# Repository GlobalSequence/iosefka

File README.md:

# Iosefka

## Specification

Iosefka is a hybrid digital analog monophonic synthesizer consisting of the following parts:

**Digital audio:**

- 2x wavetable oscillators, capable of interpolated morphing waveforms in the X and Y dimension along 256 hand-picked waveforms in a 16x16 layout
- White noise generator
- Sample-rate reduction and Bit-rate reduction effects
- Loopback digital delay fed from VCA output with feedback and adjustable rate from >3 ms to ~683 ms

**Analog audio:**

- V2140 based analog pole-mixing resonant voltage controlled filter with audio rate frequency modulation selectable between:
    - 2 pole low pass
    - 4 pole low pass
    - 2 pole high pass
    - 2 pole band pass
- LM13700 based voltage controlled amplifier
- External audio input direct into analog section and digital delay

**Step sequencer:**

- 32 step, 24 PPQ performance step sequencer
- Parameterized sequence generator including step chance, length, octave range, and musical scale
- Controls for swing, direction, clock division, first and last step, probability
- Per step Parameter locks for:
    - Note value
    - Step length
    - Velocity value
    - Step Probability
    - Single audio Parameter
- Per step mutes

**Modulation matrix to all audio Parameters:**

- 3x ADSR envelope generators (converted to control voltage for analog modules)
- 3x Low frequency oscillators (converted to control voltage for analog modules)
- Velocity control
- Aftertouch control
- Mod Wheel control
- Breath Control
- Pitch Bend Control

**MIDI Implementation:**

- **MIDI RX**
    - Note and velocity values
    - Realtime messages: clock tick, start, stop
    - CC messages for all audio Parameters (see implementation chart)
    - Modulation control of velocity, aftertouch, mod-wheel
    - Pitch bend with configurable bend range from 1 to 12 semitones
    - Program change (coming soon)
- **MIDI TX**
    - Note and velocity values (from keyboard and sequencer)
    - Realtime messages: clock tick, start, stop

**Patch storage:**

- Store 64 patches of all audio and sequencer Parameters
- Store global MIDI and machine settings

**Oscilloscope:**

- Oscillator phase locked oscilloscope with four 'time' divisions (sample divisions) between 512 to 128 samples.

# Link to the Manual
[Iosefka Manual](https://globalsequence.github.io/iosefka/#)

# Link to the Build Guide
[Build Guide - Iosefka Manual](https://globalsequence.github.io/iosefka/#build_guide/) (It's part of the manual)

# Gerber Files for Ordering the PCBs
This project includes hardware design files, as well as the gerber files which are required for PCB fabrication. The gerber files for the different boards will be found in the locations linked below. There is also a compressed zip file of all of the gerber files within this folder if that's the format your PCB fab of choice requires. 

- [iosefka bottomboard gerbers](./hardware/iosefka_bottomboard/gerbers/)
- [iosefka controlboard gerbers](./hardware/iosefka_controlboard/gerbers/)
- [iosefka motherboard gerbers](./hardware/iosefka_motherboard/gerbers)

# Bill of Materials
The three bills of materials can be found in the hardware folder of this project. 

- [iosefka boms](./hardware/boms/)

# Precompiled firmware
You can download the most current Iosefka firmware from the Releases section of this github repository. Or you can click this link: https://github.com/GlobalSequence/iosefka/releases. 

# A Note to Developers, Engineers, and People Generally Experienced in Programming and Electronics

Take this as a content warning for what you are about to see should you so much as peek into the code of this repository. It may help to frame this whole thing as a hobbyist's project that got way out of hand. I chalk any and all glaring errors up to the fundamental tension of this machine which was 'I want to create/finish this thing' vs. 'I want to learn this stuff'.

It is resoundingly true that the whole is better than the sum of its parts.

With all of that laid bare, please feel free to reach out to me about any suggestions, recommended fixes, or outright errors in both the code and the schematic. I consider the post-release critique the most enduring part of the learning process. globeseq@gmail.com 

# DISCLAIMER
This project is provided for informational and educational purposes only. By using the provided instructions, code, and hardware designs, you acknowledge that you are solely responsible for your own safety and the cost of any materials or components used.

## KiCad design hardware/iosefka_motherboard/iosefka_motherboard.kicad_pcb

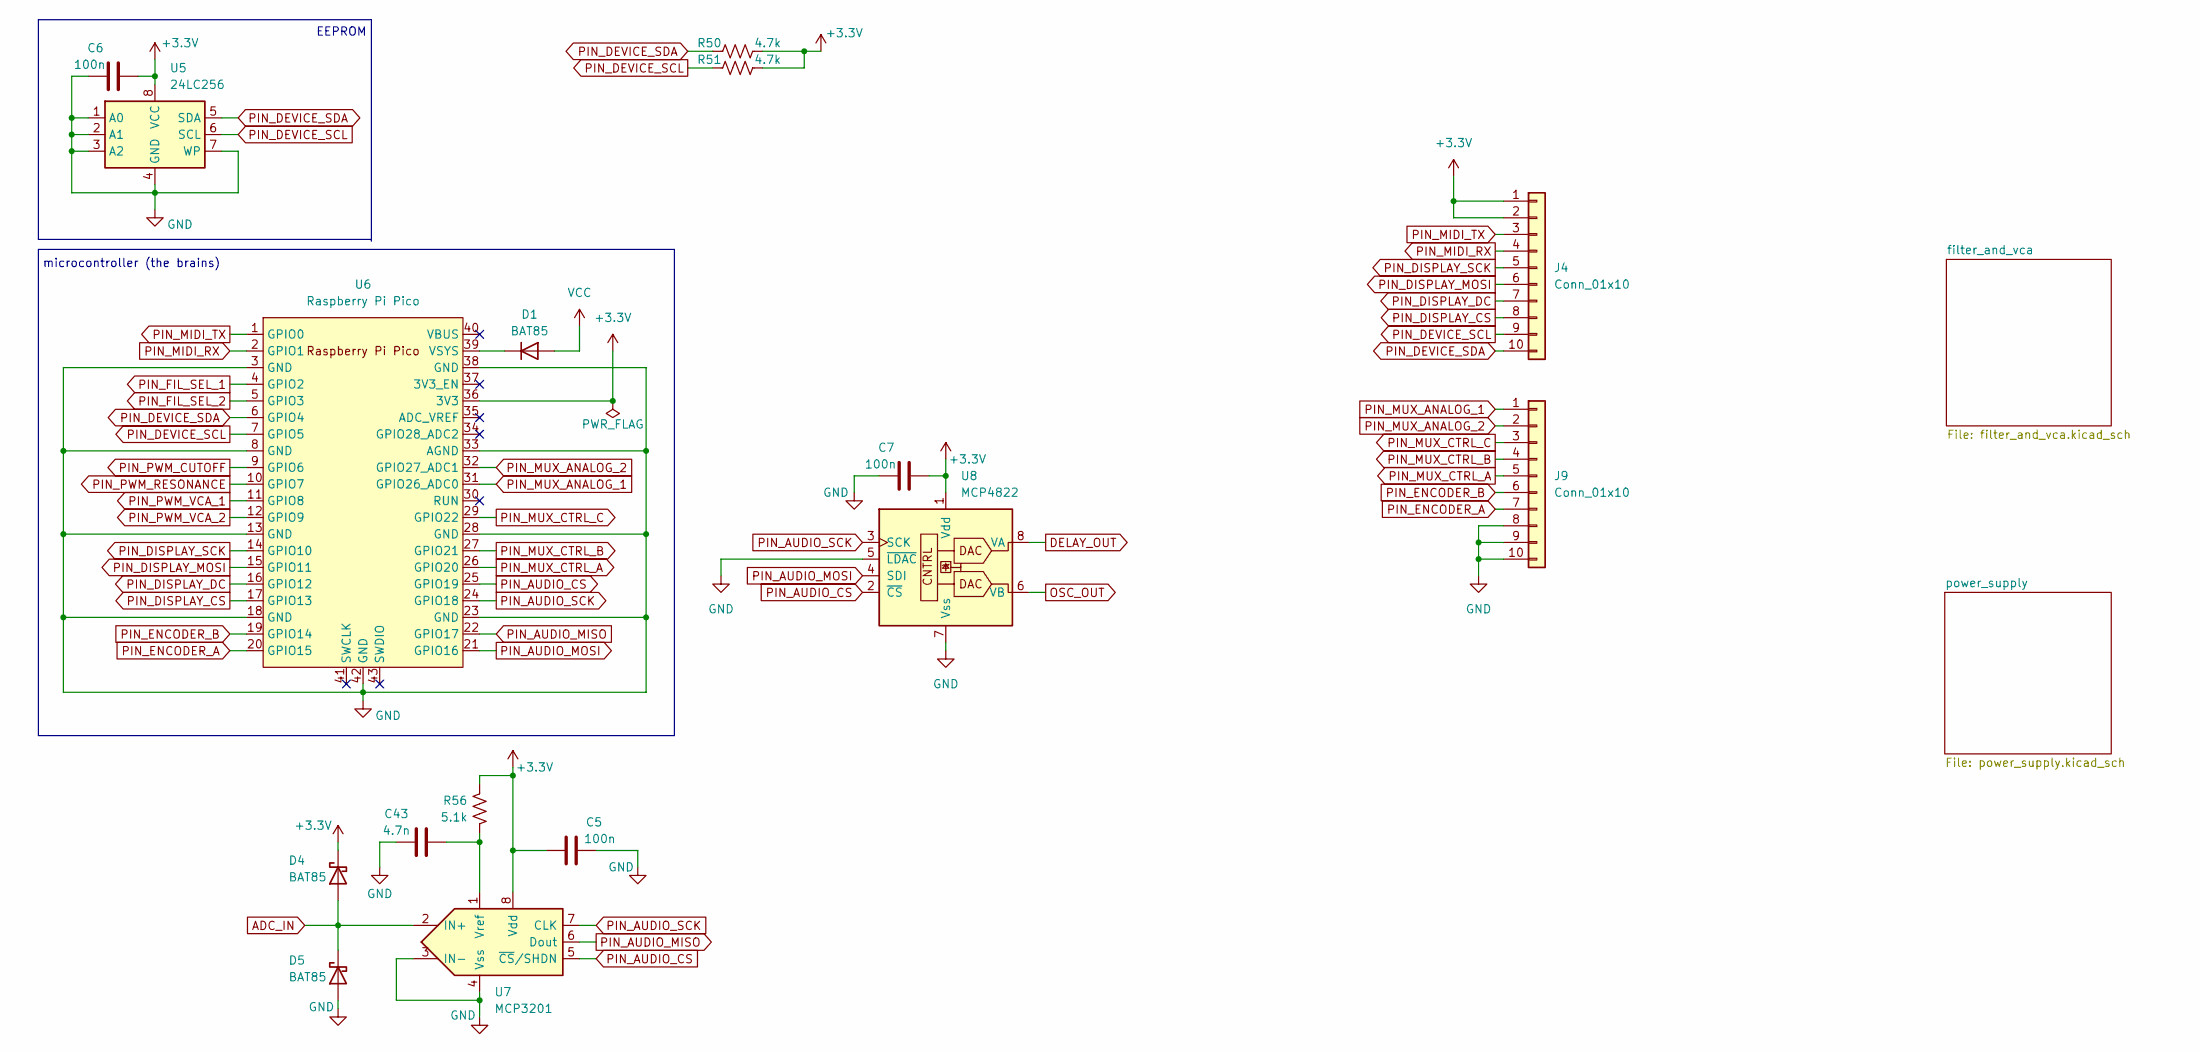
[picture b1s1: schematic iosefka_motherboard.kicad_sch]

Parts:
C5, C6, C7: 100n; C_Disc_D5.0mm_W2.5mm_P5.00mm
C43: 4.7n; C_Disc_D5.0mm_W2.5mm_P5.00mm
D1, D4, D5: BAT85; D_DO-35_SOD27_P7.62mm_Horizontal
J4, J9: Conn_01x10; PinSocket_1x10_P2.54mm_Vertical
R50, R51: 4.7k; R_Axial_DIN0207_L6.3mm_D2.5mm_P10.16mm_Horizontal
R56: 5.1k; R_Axial_DIN0207_L6.3mm_D2.5mm_P10.16mm_Horizontal
U5: 24LC256; DIP-8_W7.62mm_Socket
U6: Raspberry Pi Pico; RaspberryPi_Pico_Common_THT_NO_WIFI
U7: MCP3201; DIP-8_W7.62mm_Socket
U8: MCP4822; DIP-8_W7.62mm_Socket

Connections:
+3.3V: C5.1, C6.1, C7.1, D4.1 (K), J4.1, J4.2, R50.2, R51.2, R56.1, U5.8 (VCC), U6.36 (3V3), U7.8 (Vdd), U8.1 (Vdd)
ADC_IN: D4.2 (A), D5.1 (K), U7.2 (IN+); also elsewhere on the board
DELAY_OUT: U8.8 (VA); also elsewhere on the board
GND: C5.2, C6.2, C7.2, C43.1, D5.2 (A), J9.8, J9.9, J9.10, U5.1 (A0), U5.2 (A1), U5.3 (A2), U5.4 (GND), U5.7 (WP), U6.3 (GND), U6.8 (GND), U6.13 (GND), U6.18 (GND), U6.23 (GND), U6.28 (GND), U6.33 (AGND), U6.38 (GND), U6.42 (GND), U7.3 (IN-), U7.4 (Vss), U8.5 (~LDAC), U8.7 (Vss); also elsewhere on the board
unnamed: D1.1 (K), U6.39 (VSYS)
unnamed: C43.2, R56.2, U7.1 (Vref)
OSC_OUT: U8.6 (VB); also elsewhere on the board
PIN_AUDIO_CS: U6.25 (GPIO19), U7.5 (~CS/SHDN), U8.2 (~CS)
PIN_AUDIO_MISO: U6.22 (GPIO17), U7.6 (Dout)
PIN_AUDIO_MOSI: U6.21 (GPIO16), U8.4 (SDI)
PIN_AUDIO_SCK: U6.24 (GPIO18), U7.7 (CLK), U8.3 (SCK)
PIN_DEVICE_SCL: J4.9, R51.1, U5.6 (SCL), U6.7 (GPIO5)
PIN_DEVICE_SDA: J4.10, R50.1, U5.5 (SDA), U6.6 (GPIO4)
PIN_DISPLAY_CS: J4.8, U6.17 (GPIO13)
PIN_DISPLAY_DC: J4.7, U6.16 (GPIO12)
PIN_DISPLAY_MOSI: J4.6, U6.15 (GPIO11)
PIN_DISPLAY_SCK: J4.5, U6.14 (GPIO10)
PIN_ENCODER_A: J9.7, U6.20 (GPIO15)
PIN_ENCODER_B: J9.6, U6.19 (GPIO14)
PIN_FIL_SEL_1: U6.4 (GPIO2); also elsewhere on the board
PIN_FIL_SEL_2: U6.5 (GPIO3); also elsewhere on the board
PIN_MIDI_RX: J4.4, U6.2 (GPIO1)
PIN_MIDI_TX: J4.3, U6.1 (GPIO0)
PIN_MUX_ANALOG_1: J9.1, U6.31 (GPIO26_ADC0)
PIN_MUX_ANALOG_2: J9.2, U6.32 (GPIO27_ADC1)
PIN_MUX_CTRL_A: J9.5, U6.26 (GPIO20)
PIN_MUX_CTRL_B: J9.4, U6.27 (GPIO21)
PIN_MUX_CTRL_C: J9.3, U6.29 (GPIO22)
PIN_PWM_CUTOFF: U6.9 (GPIO6); also elsewhere on the board
PIN_PWM_RESONANCE: U6.10 (GPIO7); also elsewhere on the board
PIN_PWM_VCA_1: U6.11 (GPIO8); also elsewhere on the board
PIN_PWM_VCA_2: U6.12 (GPIO9); also elsewhere on the board
VCC: D1.2 (A); also elsewhere on the board

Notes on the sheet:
microcontroller (the brains)
EEPROM

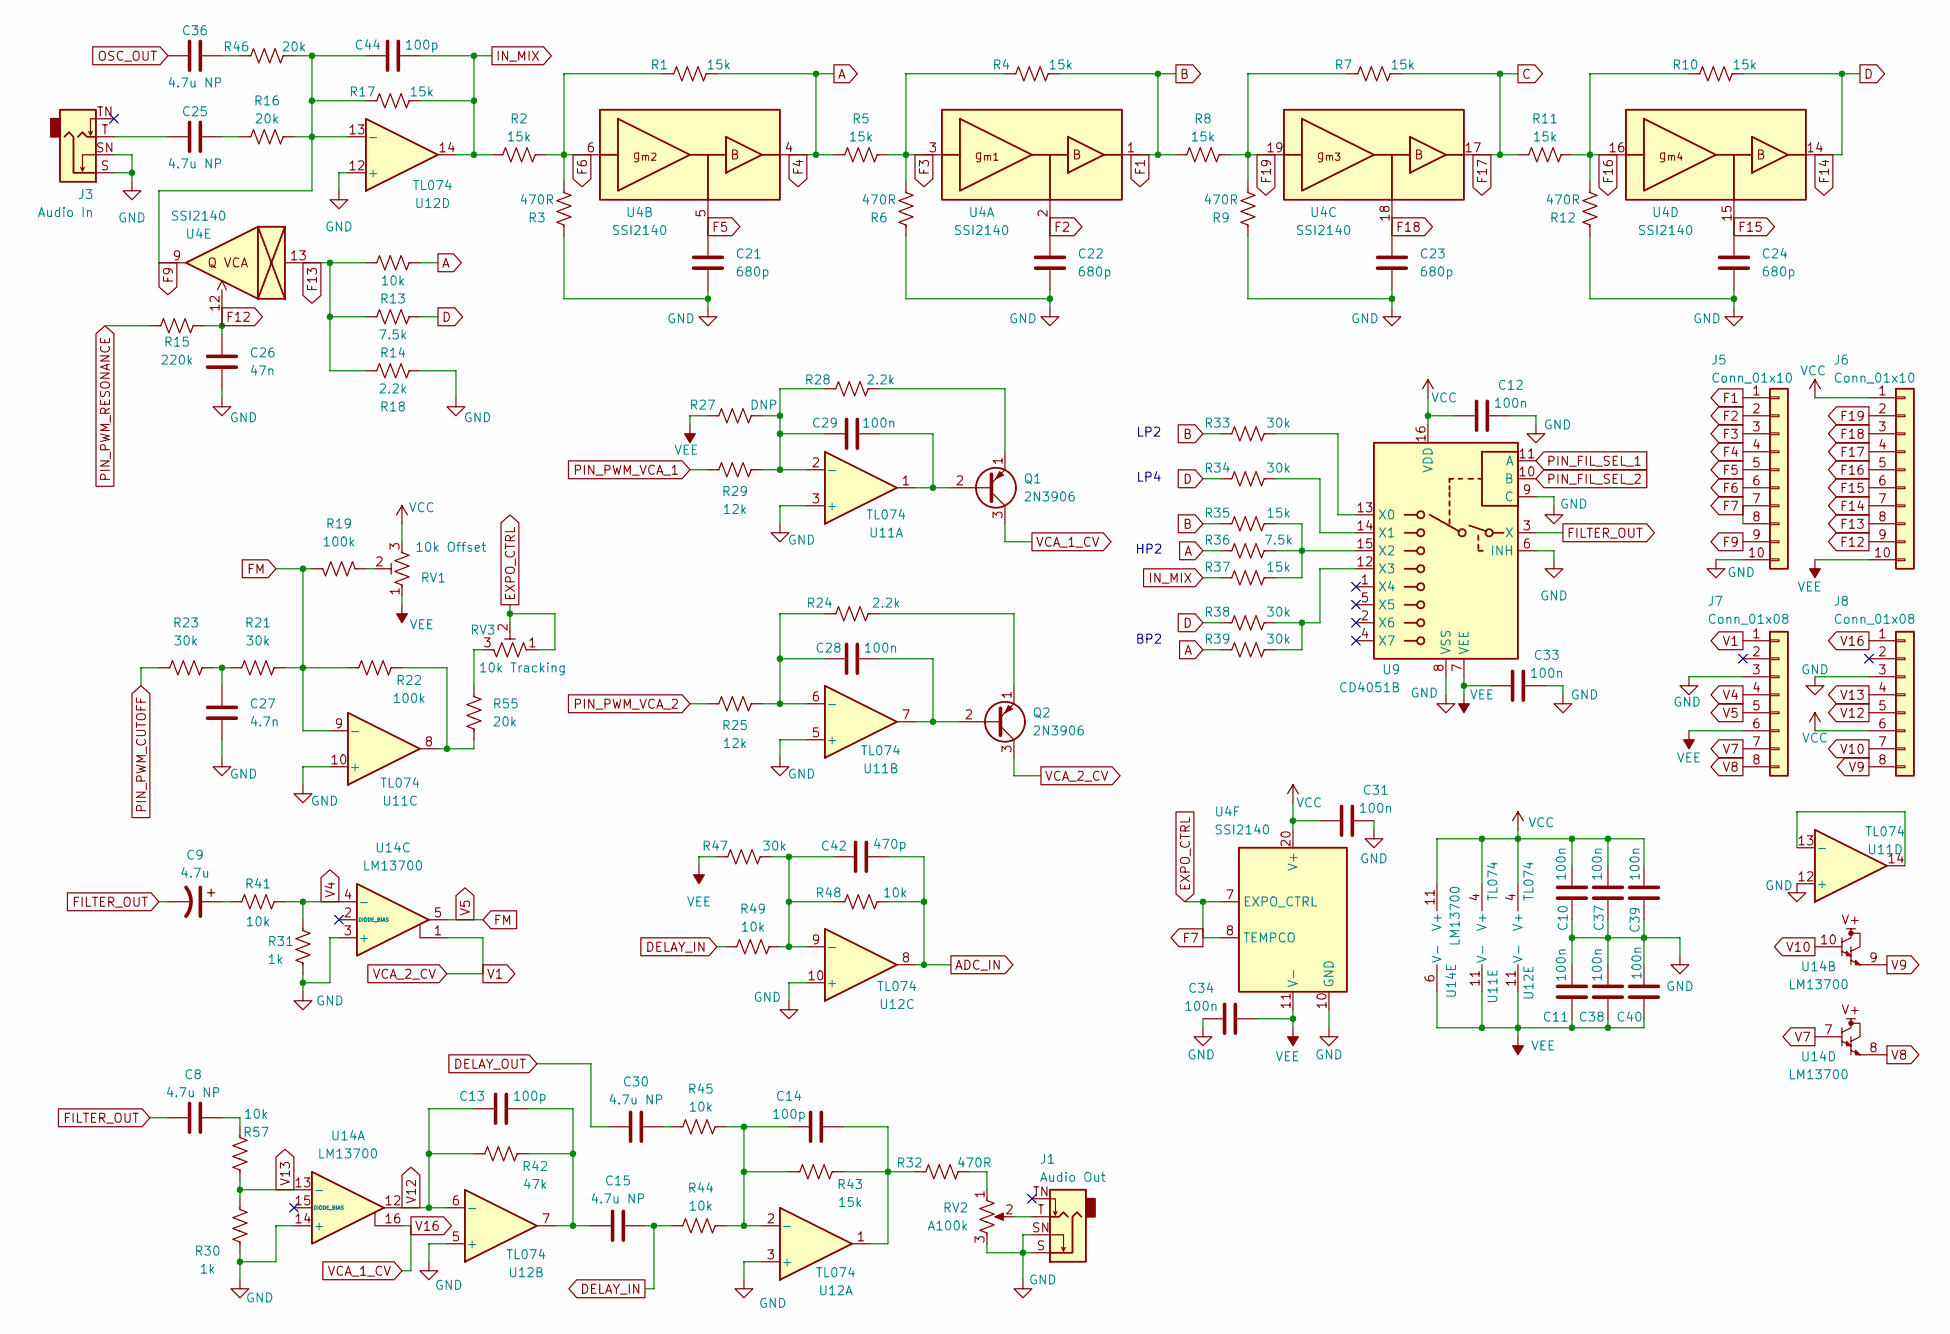
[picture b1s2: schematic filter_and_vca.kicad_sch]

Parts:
C8, C15, C25, C30, C36: 4.7u NP; CP_Radial_D6.3mm_P2.50mm_VALUE
C9: 4.7u; CP_Radial_D6.3mm_P2.50mm_VALUE
C10, C11, C12, C28, C29, C31, C33, C34, C37, C38, C39, C40: 100n; C_Disc_D5.0mm_W2.5mm_P5.00mm
C13, C14, C44: 100p; C_Disc_D5.0mm_W2.5mm_P5.00mm
C21, C22, C23, C24: 680p; C_Disc_D5.0mm_W2.5mm_P5.00mm
C26: 47n; C_Disc_D5.0mm_W2.5mm_P5.00mm
C27: 4.7n; C_Disc_D5.0mm_W2.5mm_P5.00mm
C42: 470p; C_Disc_D5.0mm_W2.5mm_P5.00mm
J1: Audio Out; Jack_6.35mm_Neutrik_NMJ4HCD2_Horizontal
J3: Audio In; Jack_6.35mm_Neutrik_NMJ4HCD2_Horizontal
J5, J6: Conn_01x10
J7, J8: Conn_01x08
Q1, Q2: 2N3906; TO-92_Inline_Wide
R1, R2, R4, R5, R7, R8, R10, R11, R17, R35, R37, R43: 15k; R_Axial_DIN0207_L6.3mm_D2.5mm_P10.16mm_Horizontal
R3, R6, R9, R12, R32: 470R; R_Axial_DIN0207_L6.3mm_D2.5mm_P10.16mm_Horizontal
R13, R41, R44, R45, R48, R49, R57: 10k; R_Axial_DIN0207_L6.3mm_D2.5mm_P10.16mm_Horizontal
R14, R36: 7.5k; R_Axial_DIN0207_L6.3mm_D2.5mm_P10.16mm_Horizontal
R15: 220k; R_Axial_DIN0207_L6.3mm_D2.5mm_P10.16mm_Horizontal
R16, R46, R55: 20k; R_Axial_DIN0207_L6.3mm_D2.5mm_P10.16mm_Horizontal
R18, R24, R28: 2.2k; R_Axial_DIN0207_L6.3mm_D2.5mm_P10.16mm_Horizontal
R19, R22: 100k; R_Axial_DIN0207_L6.3mm_D2.5mm_P10.16mm_Horizontal
R21, R23, R33, R34, R38, R39, R47: 30k; R_Axial_DIN0207_L6.3mm_D2.5mm_P10.16mm_Horizontal
R25, R29: 12k; R_Axial_DIN0207_L6.3mm_D2.5mm_P10.16mm_Horizontal
R27: DNP; R_Axial_DIN0207_L6.3mm_D2.5mm_P10.16mm_Horizontal
R30, R31: 1k; R_Axial_DIN0207_L6.3mm_D2.5mm_P10.16mm_Horizontal
R42: 47k; R_Axial_DIN0207_L6.3mm_D2.5mm_P10.16mm_Horizontal
RV1: 10k Offset; Potentiometer_Bourns_3266Z_Horizontal
RV2: A100k; Potentiometer_Bourns_PTV09A-2_Single_Horizontal
RV3: 10k Tracking; Potentiometer_Bourns_3266Z_Horizontal
U4: SSI2140; SSOP-20_5.3x7.2mm_P0.65mm
U9: CD4051B; DIP-16_W7.62mm_Socket
U11, U12: TL074; DIP-14_W7.62mm_Socket
U14: LM13700; SOIC-16_3.9x9.9mm_P1.27mm

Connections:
A: J5.4, R1.2, R5.1, R13.1, R36.1, R39.1, U4.4
ADC_IN: C42.2, R48.2, U12.8; also elsewhere on the board
B: J5.1, R4.2, R8.1, R33.1, R35.1, U4.1
C: J6.4, R7.2, R11.1, U4.17
D: J6.7, R10.2, R14.1, R34.1, R38.1, U4.14
DELAY_IN: C15.2, R44.1, R49.1
DELAY_OUT: C30.1; also elsewhere on the board
EXPO_CTRL: J5.7, J5.8, RV3.1, RV3.2, U4.7 (EXPO_CTRL), U4.8 (TEMPCO)
F2: C22.2, J5.2, U4.2
F3: J5.3, R4.1, R5.2, R6.2, U4.3
F5: C21.2, J5.5, U4.5
F6: J5.6, R1.1, R2.2, R3.2, U4.6
F9: C44.1, J5.9, R16.2, R17.1, R46.2, U4.9, U12.13 (-)
F12: C26.2, J6.9, R15.2, U4.12
F13: J6.8, R13.2, R14.2, R18.2, U4.13
F15: C24.2, J6.6, U4.15
F16: J6.5, R10.1, R11.2, R12.2, U4.16
F18: C23.2, J6.3, U4.18
F19: J6.2, R7.1, R8.2, R9.2, U4.19
FILTER_OUT: C8.1, C9.2, U9.3 (X)
FM: J7.5, R19.2, R21.2, R22.1, U11.9 (-), U14.5
GND: C10.1, C11.2, C12.2, C21.1, C22.1, C23.1, C24.1, C26.1, C27.2, C31.2, C33.2, C34.2, C37.1, C38.2, C39.1, C40.2, J1.S, J1.SN, J3.S, J3.SN, J5.10, J7.3, J8.3, R3.1, R6.1, R9.1, R12.1, R18.1, R30.2, R31.2, RV2.3, U4.10 (GND), U9.6 (INH), U9.8 (VSS), U9.9 (C), U11.3 (+), U11.5 (+), U11.10 (+), U11.12 (+), U12.3 (+), U12.5 (+), U12.10 (+), U12.12 (+), U14.3 (+), U14.14 (+); also elsewhere on the board
IN_MIX: C44.2, R2.1, R17.2, R37.1, U12.14
unnamed: C8.2, R57.2
unnamed: C9.1, R41.1
unnamed: C13.2, C15.1, R42.2, U12.7
unnamed: C14.2, R32.1, R43.2, U12.1
unnamed: C25.1, J3.T
unnamed: C25.2, R16.1
unnamed: C27.1, R21.1, R23.2
unnamed: C30.2, R45.1
unnamed: C36.2, R46.1
unnamed: J1.T, RV2.2
unnamed: C29.2, Q1.2 (B), U11.1
unnamed: Q1.1 (E), R28.2
unnamed: C28.2, Q2.2 (B), U11.7
unnamed: Q2.1 (E), R24.2
unnamed: R19.1, RV1.2
unnamed: R22.2, R55.2, U11.8
unnamed: R32.2, RV2.1
unnamed: R55.1, RV3.3
unnamed: R33.2, U9.13 (X0)
unnamed: R34.2, U9.14 (X1)
unnamed: R35.2, R36.2, R37.2, U9.15 (X2)
unnamed: R38.2, R39.2, U9.12 (X3)
unnamed: C29.1, R27.2, R28.1, R29.2, U11.2 (-)
unnamed: C28.1, R24.1, R25.2, U11.6 (-)
unnamed: U11.13 (-), U11.14
unnamed: C14.1, R43.1, R44.2, R45.2, U12.2 (-)
unnamed: C42.1, R47.2, R48.1, R49.2, U12.9 (-)
OSC_OUT: C36.1; also elsewhere on the board
PIN_FIL_SEL_1: U9.11 (A); also elsewhere on the board
PIN_FIL_SEL_2: U9.10 (B); also elsewhere on the board
PIN_PWM_CUTOFF: R23.1; also elsewhere on the board
PIN_PWM_RESONANCE: R15.1; also elsewhere on the board
PIN_PWM_VCA_1: R29.1; also elsewhere on the board
PIN_PWM_VCA_2: R25.1; also elsewhere on the board
V1: J7.1, Q2.3 (C), U14.1
V4: J7.4, R31.1, R41.2, U14.4 (-)
V7: J7.7, U14.7
V8: J7.8, U14.8
V9: J8.8, U14.9
V10: J8.7, U14.10
V12: C13.1, J8.5, R42.1, U12.6 (-), U14.12
V13: J8.4, R30.1, R57.1, U14.13 (-)
V16: J8.1, Q1.3 (C), U14.16
VCC: C10.2, C12.1, C31.1, C37.2, C39.2, J6.1, J8.6, RV1.3, U4.20 (V+), U9.16 (VDD), U11.4 (V+), U12.4 (V+), U14.11 (V+); also elsewhere on the board
VEE: C11.1, C33.1, C34.1, C38.1, C40.1, J6.10, J7.6, R27.1, R47.1, RV1.1, U4.11 (V-), U9.7 (VEE), U11.11 (V-), U12.11 (V-), U14.6 (V-); also elsewhere on the board

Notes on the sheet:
BP2
LP2
LP4
HP2

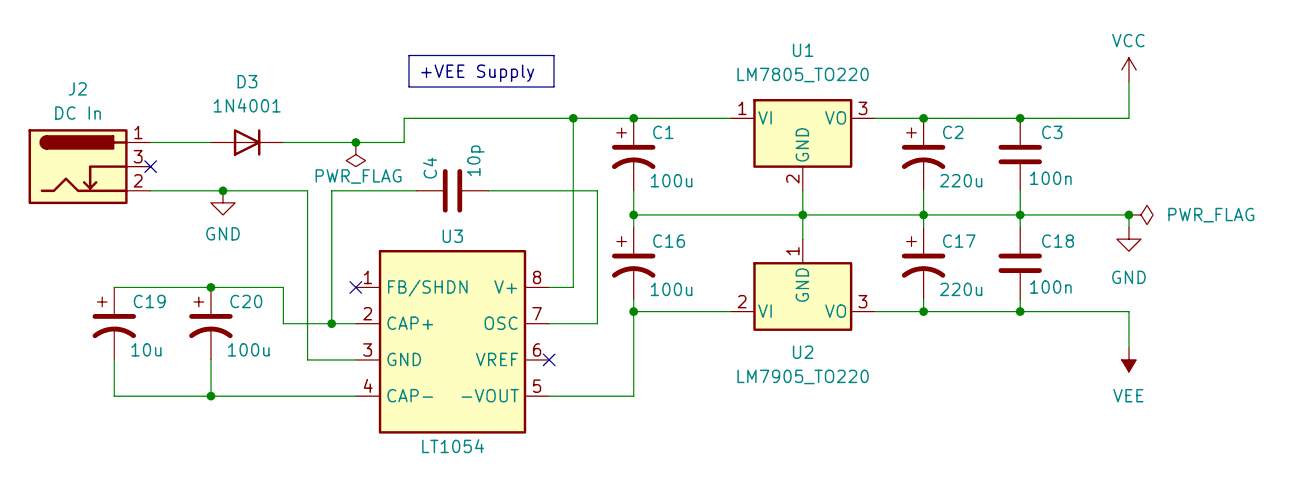
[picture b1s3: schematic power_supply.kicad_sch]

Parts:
C1, C16, C20: 100u; CP_Radial_D6.3mm_P2.50mm_VALUE
C2, C17: 220u; CP_Radial_D8.0mm_P2.50mm_VALUE
C3, C18: 100n; C_Disc_D5.0mm_W2.5mm_P5.00mm
C4: 10p; C_Disc_D5.0mm_W2.5mm_P5.00mm
C19: 10u; CP_Radial_D5.0mm_P2.50mm
D3: 1N4001; D_DO-41_SOD81_P10.16mm_Horizontal
J2: DC In; BarrelJack_Horizontal
U1: LM7805_TO220; TO-220-3_Horizontal_TabDown
U2: LM7905_TO220; TO-220-3_Horizontal_TabDown
U3: LT1054; DIP-8_W7.62mm_Socket

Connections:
GND: C1.2, C2.2, C3.2, C16.1, C17.1, C18.1, J2.2, U1.2 (GND), U2.1 (GND), U3.3 (GND); also elsewhere on the board
unnamed: D3.2 (A), J2.1
unnamed: C1.1, D3.1 (K), U1.1 (VI), U3.8 (V+)
unnamed: C16.2, U2.2 (VI), U3.5 (-VOUT)
unnamed: C4.1, C19.1, C20.1, U3.2 (CAP+)
unnamed: C19.2, C20.2, U3.4 (CAP-)
unnamed: C4.2, U3.7 (OSC)
VCC: C2.1, C3.1, U1.3 (VO); also elsewhere on the board
VEE: C17.2, C18.2, U2.3 (VO); also elsewhere on the board

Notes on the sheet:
+VEE Supply

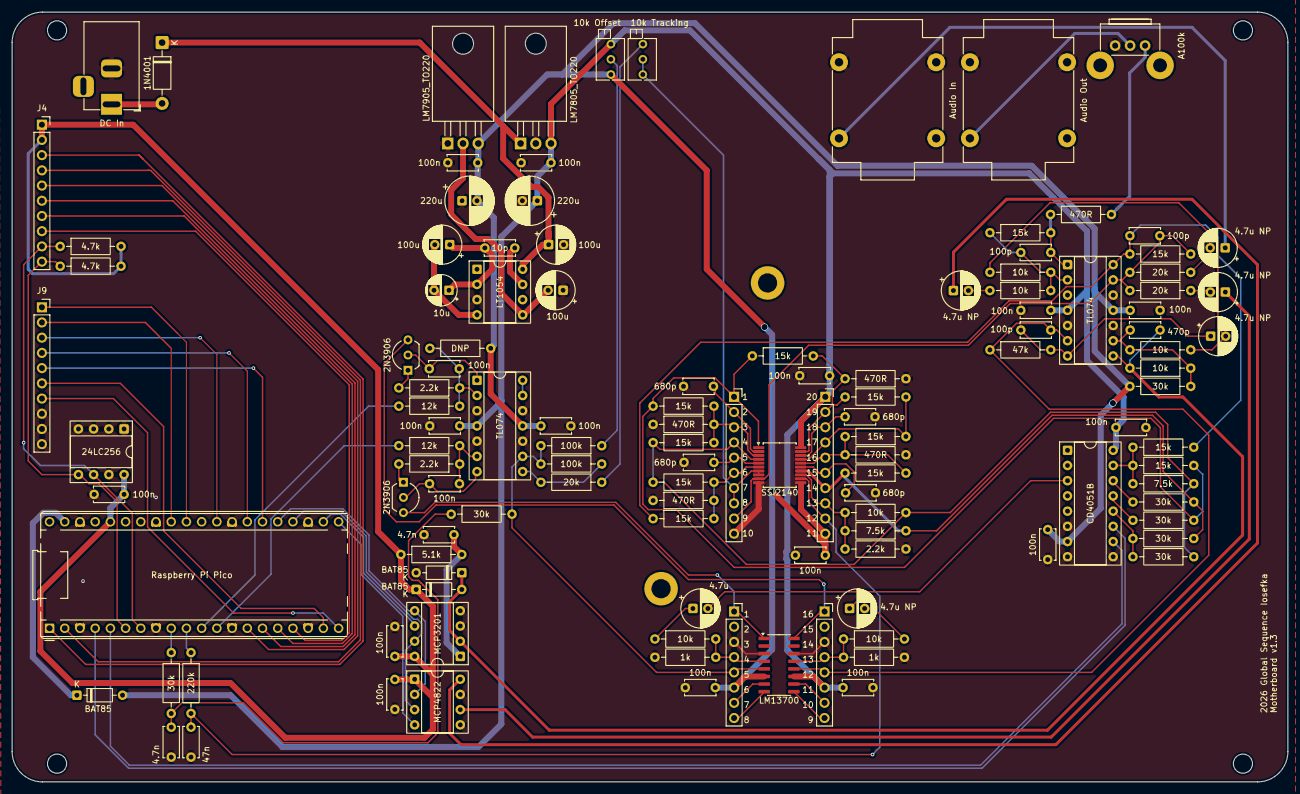
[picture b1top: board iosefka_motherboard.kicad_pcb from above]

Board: 2 copper layers, 213.0 x 128.5 mm, 122 parts (0 on the bottom side), 96 nets.

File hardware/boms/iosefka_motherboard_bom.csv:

Reference,Value,Datasheet,Footprint,Qty,Comments
"C1,C16,C20",100u,,values_not_refs:CP_Radial_D6.3mm_P2.50mm_VALUE,3,
"C2,C17",220u,,values_not_refs:CP_Radial_D8.0mm_P2.50mm_VALUE,2,
"C3,C5,C6,C7,C10,C11,C12,C18,C28,C29,C31,C33,C34,C37,C38,C39,C40",100n,,Capacitor_THT:C_Disc_D5.0mm_W2.5mm_P5.00mm,17,
C4,10p,,Capacitor_THT:C_Disc_D5.0mm_W2.5mm_P5.00mm,1,
"C8,C15,C25,C30,C36",4.7u NP,,values_not_refs:CP_Radial_D6.3mm_P2.50mm_VALUE,5,Non-polar audio capacitors. Will not work with standard electrolytics.
C9,4.7u,,values_not_refs:CP_Radial_D6.3mm_P2.50mm_VALUE,1,
"C13,C14,C44",100p,,Capacitor_THT:C_Disc_D5.0mm_W2.5mm_P5.00mm,3,
C19,10u,,Capacitor_THT:CP_Radial_D5.0mm_P2.50mm,1,
"C21,C22,C23,C24",680p,,Capacitor_THT:C_Disc_D5.0mm_W2.5mm_P5.00mm,4,
C26,47n,,Capacitor_THT:C_Disc_D5.0mm_W2.5mm_P5.00mm,1,
"C27,C43",4.7n,,Capacitor_THT:C_Disc_D5.0mm_W2.5mm_P5.00mm,2,
C42,470p,,Capacitor_THT:C_Disc_D5.0mm_W2.5mm_P5.00mm,1,
"D1,D4,D5",BAT85,https://assets.nexperia.com/documents/data-sheet/BAT85.pdf,Diode_THT:D_DO-35_SOD27_P7.62mm_Horizontal,3,
D3,1N4001,http://www.vishay.com/docs/88503/1n4001.pdf,Diode_THT:D_DO-41_SOD81_P10.16mm_Horizontal,1,
J1,Audio Out,,Connector_Audio:Jack_6.35mm_Neutrik_NMJ4HCD2_Horizontal,1,
J2,DC In,,Connector_BarrelJack:BarrelJack_Horizontal,1,
J3,Audio In,,Connector_Audio:Jack_6.35mm_Neutrik_NMJ4HCD2_Horizontal,1,
"J4,J5,J6,J9",Conn_01x10,,Connector_PinSocket_2.54mm:PinSocket_1x10_P2.54mm_Vertical,4,These are female pin sockets. 2 of 4 are optional if you plan to solder the SSI2140 directly to the PCB.
"J7,J8",Conn_01x08,,,2,These are female pin sockets. These are optional if you plan to solder the LM13700 directly to the PCB. 
,Conn_01x10,,,2,Male pin headers. These are optional if you plan to solder the SSI2140 directly to the PCB.
,Conn_01x08,,,2,Male pin headers. These are optional if you plan to solder the LM13700 directly to the PCB. 
"Q1,Q2",2N3906,https://www.onsemi.com/pub/Collateral/2N3906-D.PDF,values_not_refs:TO-92_Inline_Wide,2,
"R1,R2,R4,R5,R7,R8,R10,R11,R17,R35,R37,R43",15k,,Resistor_THT:R_Axial_DIN0207_L6.3mm_D2.5mm_P10.16mm_Horizontal,12,"All resistors ¼W, 1% metal film recommended"
"R3,R6,R9,R12,R32",470R,,Resistor_THT:R_Axial_DIN0207_L6.3mm_D2.5mm_P10.16mm_Horizontal,5,
"R13,R41,R44,R45,R48,R49,R57",10k,,Resistor_THT:R_Axial_DIN0207_L6.3mm_D2.5mm_P10.16mm_Horizontal,7,
"R14,R36",7.5k,,Resistor_THT:R_Axial_DIN0207_L6.3mm_D2.5mm_P10.16mm_Horizontal,2,
R15,220k,,Resistor_THT:R_Axial_DIN0207_L6.3mm_D2.5mm_P10.16mm_Horizontal,1,
"R16,R46,R55",20k,,Resistor_THT:R_Axial_DIN0207_L6.3mm_D2.5mm_P10.16mm_Horizontal,3,
"R18,R24,R28",2.2k,,Resistor_THT:R_Axial_DIN0207_L6.3mm_D2.5mm_P10.16mm_Horizontal,3,
"R19,R22",100k,,Resistor_THT:R_Axial_DIN0207_L6.3mm_D2.5mm_P10.16mm_Horizontal,2,
"R21,R23,R33,R34,R38,R39,R47",30k,,Resistor_THT:R_Axial_DIN0207_L6.3mm_D2.5mm_P10.16mm_Horizontal,7,
"R25,R29",12k,,Resistor_THT:R_Axial_DIN0207_L6.3mm_D2.5mm_P10.16mm_Horizontal,2,
R27,DNP,,Resistor_THT:R_Axial_DIN0207_L6.3mm_D2.5mm_P10.16mm_Horizontal,1,DNP = Do not place. No resistor goes here. It's a vestige from an older version of the schematic. 
"R30,R31",1k,,Resistor_THT:R_Axial_DIN0207_L6.3mm_D2.5mm_P10.16mm_Horizontal,2,
R42,47k,,Resistor_THT:R_Axial_DIN0207_L6.3mm_D2.5mm_P10.16mm_Horizontal,1,
"R50,R51",4.7k,,Resistor_THT:R_Axial_DIN0207_L6.3mm_D2.5mm_P10.16mm_Horizontal,2,
R56,5.1k,,Resistor_THT:R_Axial_DIN0207_L6.3mm_D2.5mm_P10.16mm_Horizontal,1,
"RV1, RV3","10k Offset, 10k Tracking",,Potentiometer_THT:Potentiometer_Bourns_3266Z_Horizontal,2,Recommended Model: Bourns 3296X-1-103LF 
RV2,A100k,,Potentiometer_THT:Potentiometer_Bourns_PTV09A-2_Single_Horizontal,1,"Recommended model: Bourns PTV09A-2015U-B103. Note that this is NOT a logarithmic pot as the schematic recommends. If you can find a horizontal pot that is, use that one, and tell me where you found it!"
U1,LM7805_TO220,https://www.onsemi.cn/PowerSolutions/document/MC7800-D.PDF,Package_TO_SOT_THT:TO-220-3_Horizontal_TabDown,1,
U2,LM7905_TO220,https://www.onsemi.com/pub/Collateral/MC7900-D.PDF,Package_TO_SOT_THT:TO-220-3_Horizontal_TabDown,1,
U3,LT1054,https://www.analog.com/media/en/technical-documentation/data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,Package_DIP:DIP-8_W7.62mm_Socket,1,
U4,SSI2140,https://www.soundsemiconductor.com/downloads/ssi2140datasheet.pdf,Package_SO:SSOP-20_5.3x7.2mm_P0.65mm,1,
U5,24LC256,http://ww1.microchip.com/downloads/en/devicedoc/21203m.pdf,Package_DIP:DIP-8_W7.62mm_Socket,1,
U6,Raspberry Pi Pico,,Module:RaspberryPi_Pico_Common_THT_NO_WIFI,1,"This is the Raspberry Pi Pico 1, with the RP2040 chip. This has not been tested with the RP2350 or other models. "
U7,MCP3201,http://ww1.microchip.com/downloads/en/DeviceDoc/21290D.pdf,Package_DIP:DIP-8_W7.62mm_Socket,1,
U8,MCP4822,http://ww1.microchip.com/downloads/en/DeviceDoc/20002249B.pdf,Package_DIP:DIP-8_W7.62mm_Socket,1,
U9,CD4051B,http://www.ti.com/lit/ds/symlink/cd4052b.pdf,Package_DIP:DIP-16_W7.62mm_Socket,1,
"U11,U12",TL074,http://www.ti.com/lit/ds/symlink/tl071.pdf,Package_DIP:DIP-14_W7.62mm_Socket,2,
U14,LM13700,http://www.ti.com/lit/ds/symlink/lm13700.pdf,Package_SO:SOIC-16_3.9x9.9mm_P1.27mm,1,
,"16 pin dip socket, 7.26mm row pitch",,,1,
,"14 pin dip socket, 7.26mm row pitch",,,2,
,"8 pin dip socket, 7.26mm row pitch",,,4,
,SSI2140 Breakout,,,1,Gerber files found here. This is optional if you plan to solder the SSI2140 directly to the PCB. 
,LM13700 Breakout,,,1,Gerber files found here. This is optional if you plan to solder the LM13700 directly to the PCB.

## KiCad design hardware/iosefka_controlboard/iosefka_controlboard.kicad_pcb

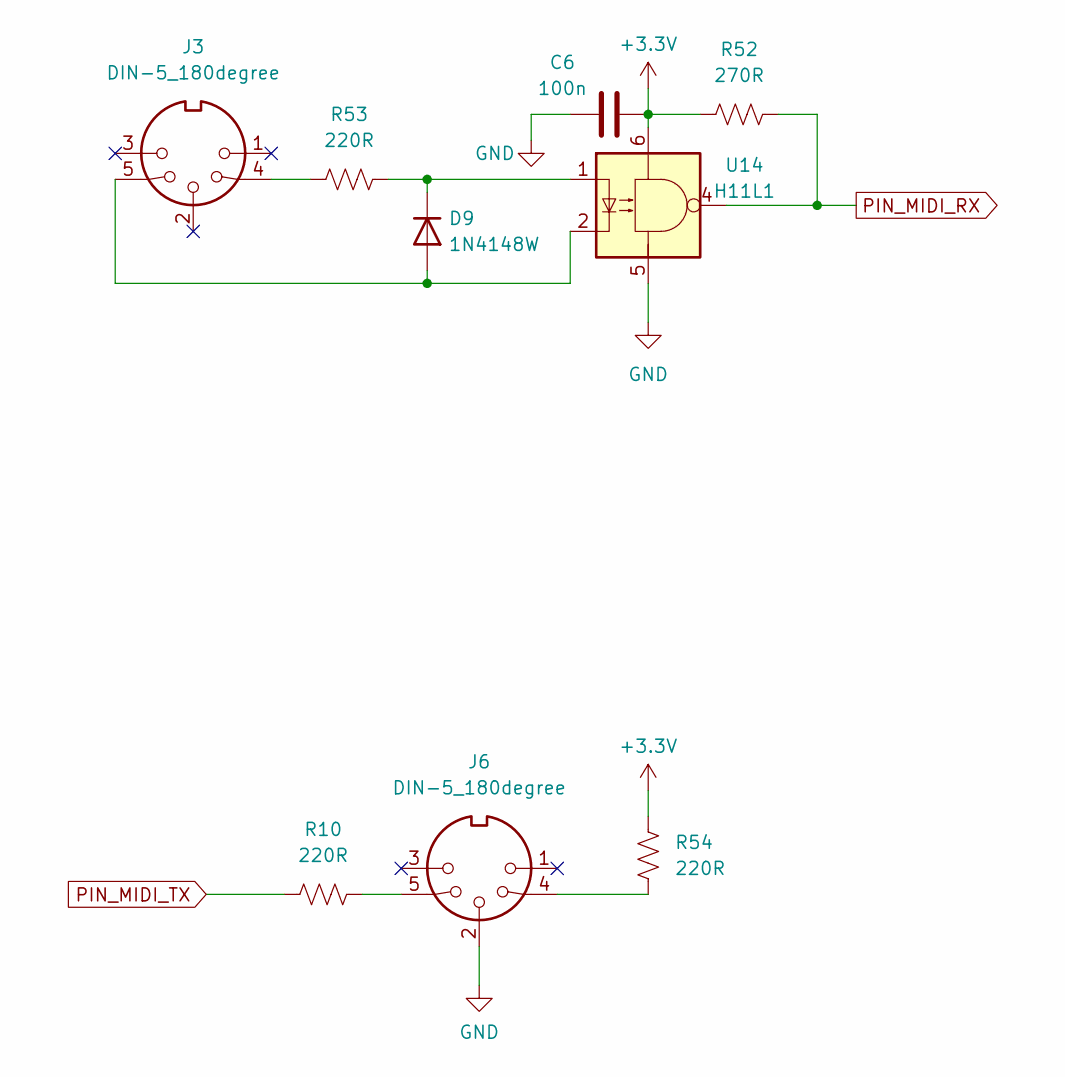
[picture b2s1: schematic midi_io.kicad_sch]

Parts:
C6: 100n; C_Rect_L7.0mm_W2.0mm_P5.00mm
D9: 1N4148W; D_DO-35_SOD27_P7.62mm_Horizontal
J3, J6: DIN-5_180degree; MIDI_DIN5
R10, R53, R54: 220R; R_Axial_DIN0207_L6.3mm_D2.5mm_P10.16mm_Horizontal
R52: 270R; R_Axial_DIN0207_L6.3mm_D2.5mm_P10.16mm_Horizontal
U14: H11L1; DIP-6_W7.62mm_Socket

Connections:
+3.3V: C6.2, R52.1, R54.1, U14.6; also elsewhere on the board
GND: C6.1, J6.2, U14.5; also elsewhere on the board
unnamed: D9.2 (A), J3.5, U14.2
unnamed: D9.1 (K), R53.2, U14.1
unnamed: J3.4, R53.1
unnamed: J6.4, R54.2
unnamed: J6.5, R10.2
PIN_MIDI_RX: R52.2, U14.4; also elsewhere on the board
PIN_MIDI_TX: R10.1; also elsewhere on the board

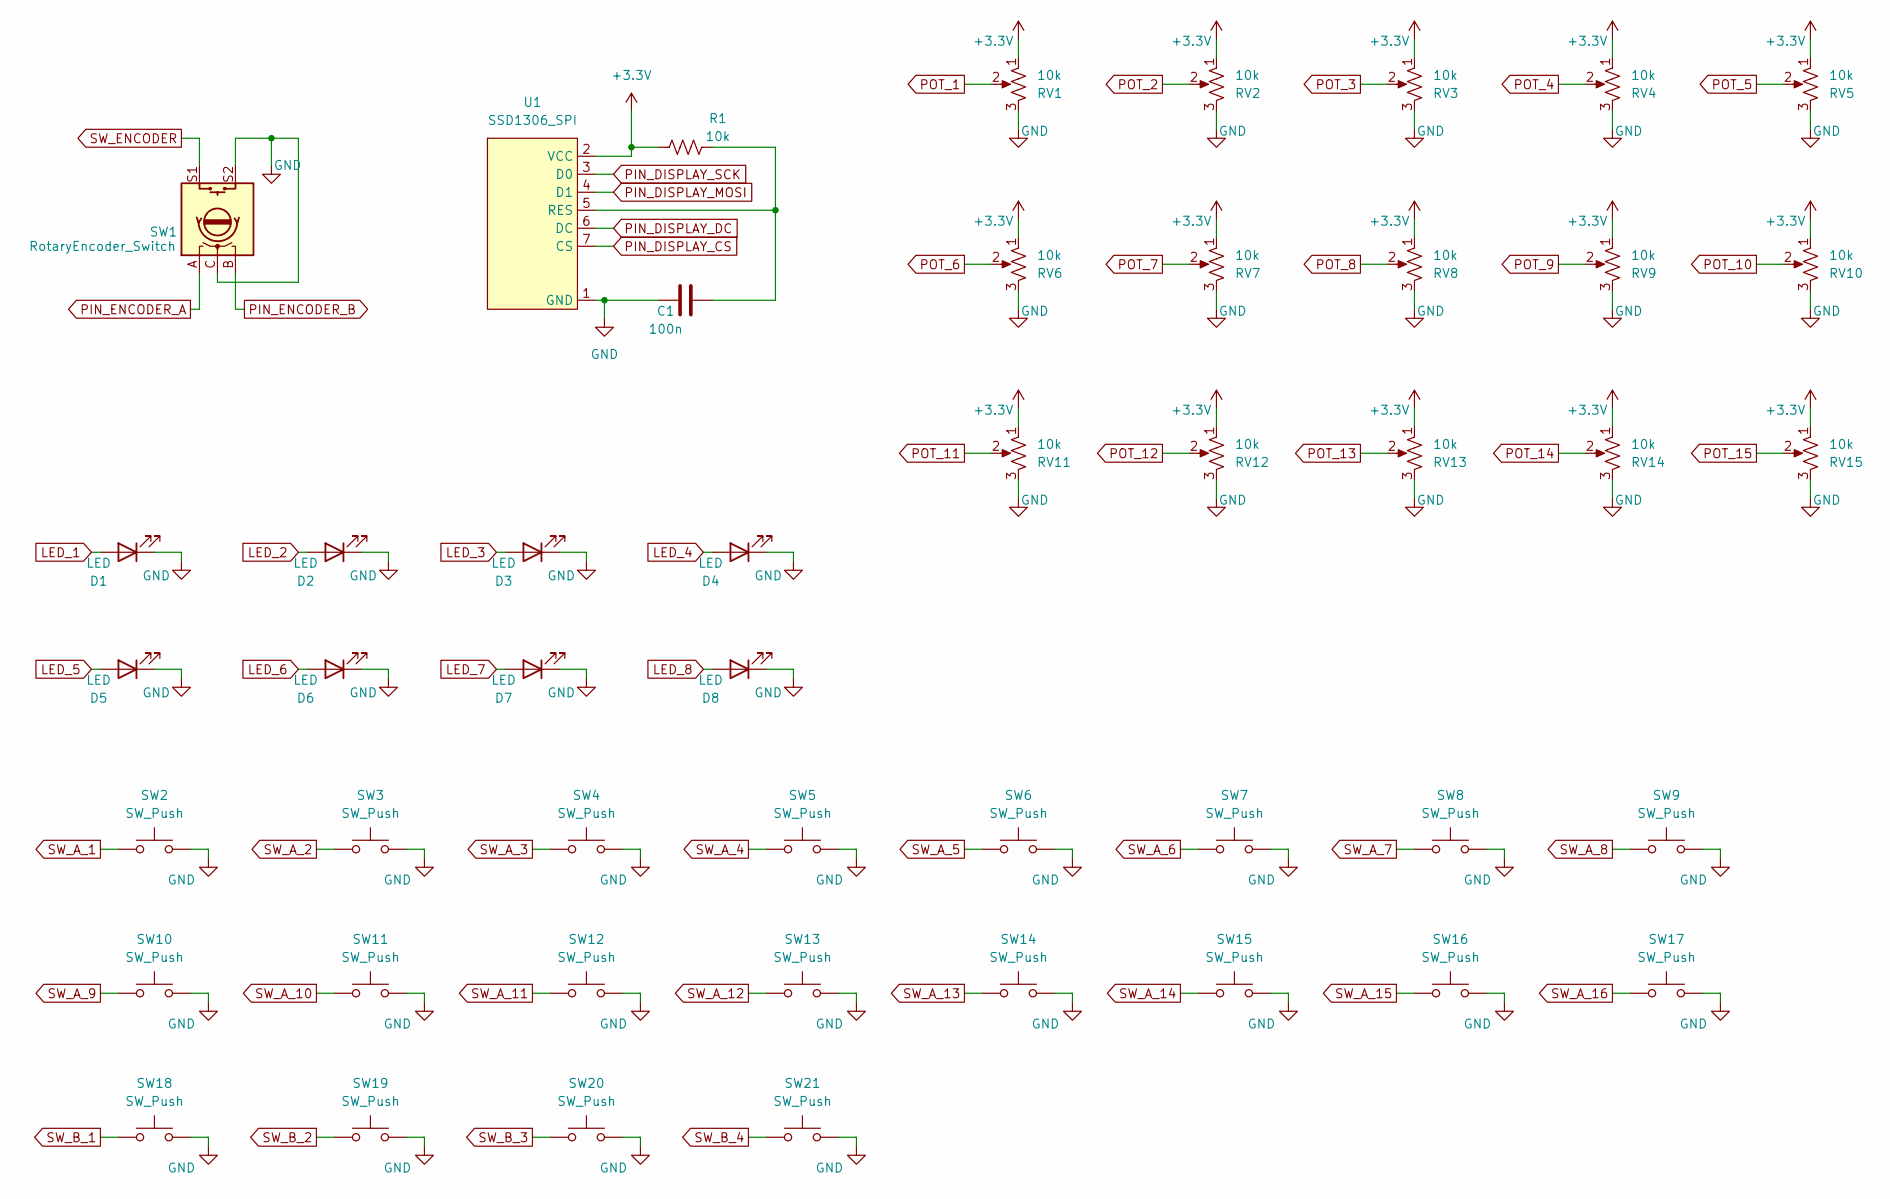
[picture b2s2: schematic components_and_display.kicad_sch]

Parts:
C1: 100n; C_Rect_L7.0mm_W2.0mm_P5.00mm
D1, D2, D3, D4, D5, D6, D7, D8: LED; LED_D3.0mm
R1: 10k; R_Axial_DIN0207_L6.3mm_D2.5mm_P10.16mm_Horizontal
RV1, RV2, RV3, RV4, RV5, RV6, RV7, RV8, RV9, RV10, RV11, RV12, RV13, RV14, RV15: 10k; Potentiometer_Bourns_PTV09A-1_Single_Vertical
SW1: RotaryEncoder_Switch; RotaryEncoder_Alps_EC11E-Switch_Vertical_H20mm
SW2, SW3, SW4, SW5, SW6, SW7, SW8, SW9, SW10, SW11, SW12, SW13, SW14, SW15, SW16, SW17, SW18, SW19, SW20, SW21: SW_Push; SW_PUSH_6mm
U1: SSD1306_SPI; 128x64_0.96_Disp_Module

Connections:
+3.3V: R1.1, RV1.1, RV2.1, RV3.1, RV4.1, RV5.1, RV6.1, RV7.1, RV8.1, RV9.1, RV10.1, RV11.1, RV12.1, RV13.1, RV14.1, RV15.1, U1.2 (VCC); also elsewhere on the board
GND: C1.1, D1.1 (K), D2.1 (K), D3.1 (K), D4.1 (K), D5.1 (K), D6.1 (K), D7.1 (K), D8.1 (K), RV1.3, RV2.3, RV3.3, RV4.3, RV5.3, RV6.3, RV7.3, RV8.3, RV9.3, RV10.3, RV11.3, RV12.3, RV13.3, RV14.3, RV15.3, SW1.C, SW1.S2, SW2.2, SW3.2, SW4.2, SW5.2, SW6.2, SW7.2, SW8.2, SW9.2, SW10.2, SW11.2, SW12.2, SW13.2, SW14.2, SW15.2, SW16.2, SW17.2, SW18.2, SW19.2, SW20.2, SW21.2, U1.1 (GND); also elsewhere on the board
LED_1: D1.2 (A); also elsewhere on the board
LED_2: D2.2 (A); also elsewhere on the board
LED_3: D3.2 (A); also elsewhere on the board
LED_4: D4.2 (A); also elsewhere on the board
LED_5: D5.2 (A); also elsewhere on the board
LED_6: D6.2 (A); also elsewhere on the board
LED_7: D7.2 (A); also elsewhere on the board
LED_8: D8.2 (A); also elsewhere on the board
unnamed: C1.2, R1.2, U1.5 (RES)
PIN_DISPLAY_CS: U1.7 (CS); also elsewhere on the board
PIN_DISPLAY_DC: U1.6 (DC); also elsewhere on the board
PIN_DISPLAY_MOSI: U1.4 (D1); also elsewhere on the board
PIN_DISPLAY_SCK: U1.3 (D0); also elsewhere on the board
PIN_ENCODER_A: SW1.A; also elsewhere on the board
PIN_ENCODER_B: SW1.B; also elsewhere on the board
POT_1: RV1.2; also elsewhere on the board
POT_2: RV2.2; also elsewhere on the board
POT_3: RV3.2; also elsewhere on the board
POT_4: RV4.2; also elsewhere on the board
POT_5: RV5.2; also elsewhere on the board
POT_6: RV6.2; also elsewhere on the board
POT_7: RV7.2; also elsewhere on the board
POT_8: RV8.2; also elsewhere on the board
POT_9: RV9.2; also elsewhere on the board
POT_10: RV10.2; also elsewhere on the board
POT_11: RV11.2; also elsewhere on the board
POT_12: RV12.2; also elsewhere on the board
POT_13: RV13.2; also elsewhere on the board
POT_14: RV14.2; also elsewhere on the board
POT_15: RV15.2; also elsewhere on the board
SW_A_1: SW2.1; also elsewhere on the board
SW_A_2: SW3.1; also elsewhere on the board
SW_A_3: SW4.1; also elsewhere on the board
SW_A_4: SW5.1; also elsewhere on the board
SW_A_5: SW6.1; also elsewhere on the board
SW_A_6: SW7.1; also elsewhere on the board
SW_A_7: SW8.1; also elsewhere on the board
SW_A_8: SW9.1; also elsewhere on the board
SW_A_9: SW10.1; also elsewhere on the board
SW_A_10: SW11.1; also elsewhere on the board
SW_A_11: SW12.1; also elsewhere on the board
SW_A_12: SW13.1; also elsewhere on the board
SW_A_13: SW14.1; also elsewhere on the board
SW_A_14: SW15.1; also elsewhere on the board
SW_A_15: SW16.1; also elsewhere on the board
SW_A_16: SW17.1; also elsewhere on the board
SW_B_1: SW18.1; also elsewhere on the board
SW_B_2: SW19.1; also elsewhere on the board
SW_B_3: SW20.1; also elsewhere on the board
SW_B_4: SW21.1; also elsewhere on the board
SW_ENCODER: SW1.S1; also elsewhere on the board
